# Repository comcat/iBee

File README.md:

iBee PCB Quadcopter
========================

[*iBee Quadcopter Board PCB Layout (iBee V0.8)*](https://www.jackslab.org/)

[*iBee Quadcopter Board PCB (iBee V0.8)*](https://www.jackslab.org/)

It's based on the control board of Flexbot Quadcopter.

Repository Contents
-------------------
* hardware/V0.8/ - All Eagle design files (.brd, .sch) and Gerber files of iBee version 0.8

License Information
-------------------
The hardware is released under [Creative Commons ShareAlike 4.0 International](https://creativecommons.org/licenses/by-sa/4.0/).

Distributed as-is; no warranty is given.

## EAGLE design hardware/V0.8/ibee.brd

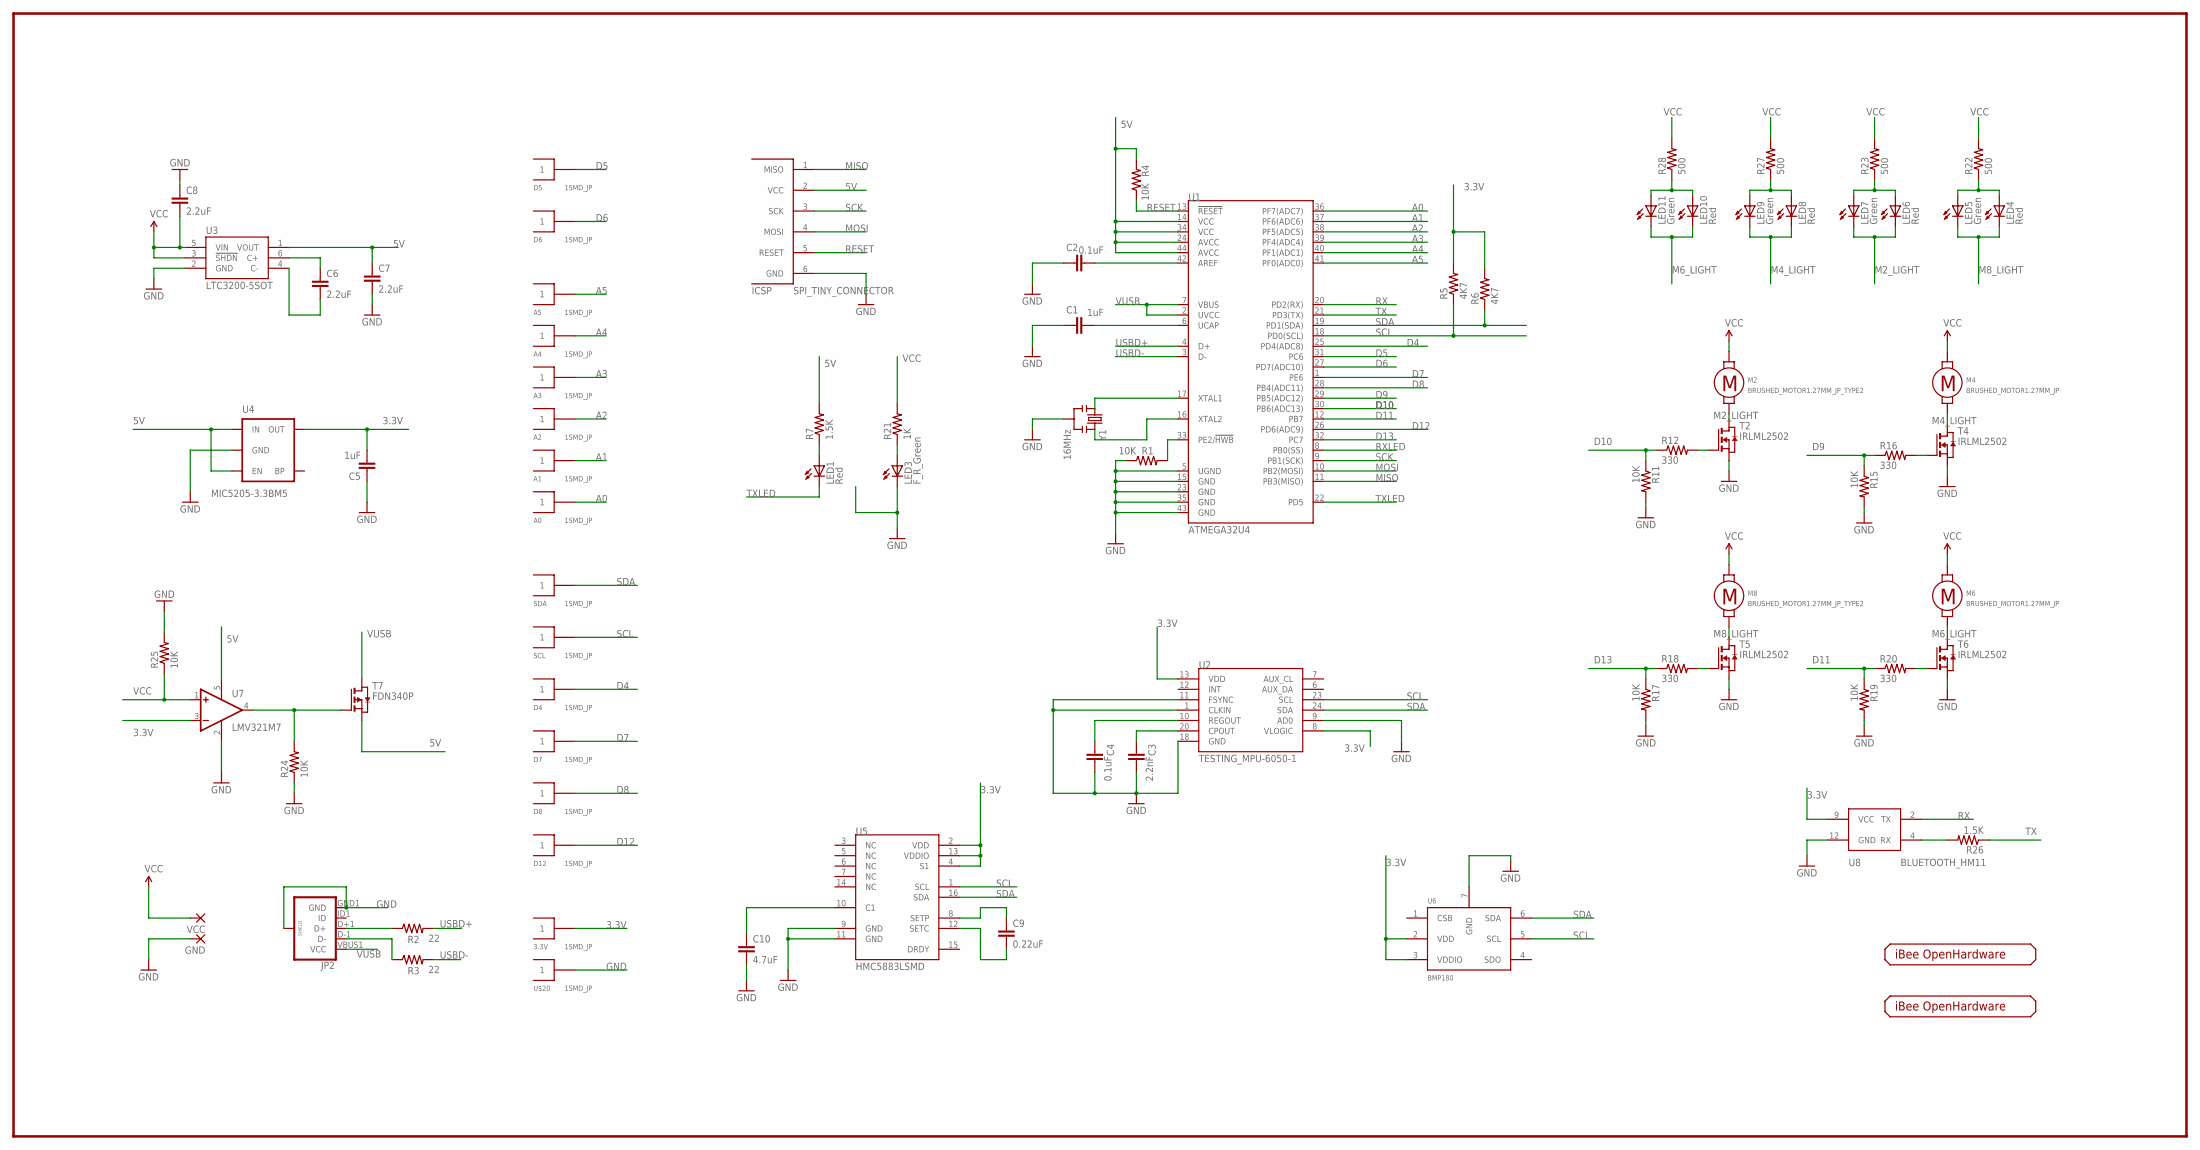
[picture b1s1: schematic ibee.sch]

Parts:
3.3V: 1SMD_JP; 1SMD
A0, A1, A2, A3, A4, A5: 1SMD_JP; 1SMD
C1, C5: 1uF; 0402-CAP
C2, C4: 0.1uF; 0402-CAP
C3: 2.2nF; 0402-CAP
C6, C7, C8: 2.2uF; 0603-CAP
C9: 0.22uF; 0402-CAP
C10: 4.7uF; 0603-CAP
D4, D5, D6, D7, D8, D12: 1SMD_JP; 1SMD
GND: 2,15/1,0
ICSP: SPI_TINY_CONNECTOR; AVR_ISP_TINY_CONNECTOR_NO_BORDER
JP2: USB_MICROB_PLUGCONN-11752; USB-B-MICRO-SMD_V03
LED1, LED4, LED6, LED8, LED10: Red; CHIPLED_0603
LED3: F_R_Green; CHIPLED_0603
LED5, LED7, LED9, LED11: Green; CHIPLED_0603
M2, M8: BRUSHED_MOTOR1.27MM_JP_TYPE2; BRUSHED_MOTOR_1.27MM_JP_TYPE2
M4, M6: BRUSHED_MOTOR1.27MM_JP; BRUSHED_MOTOR_1.27MM_JP
R1, R4, R11, R15, R17, R19, R24, R25: 10K; 0402-RES
R2, R3: 22; 0402-RES
R5, R6: 4K7; 0402-RES
R7, R26: 1.5K; 0402-RES
R12, R16, R18, R20: 330; 0402-RES
R21: 1K; 0402-RES
R22, R23, R27, R28: 500; 0402-RES
SCL: 1SMD_JP; 1SMD
SDA: 1SMD_JP; 1SMD
T2, T4, T5, T6: IRLML2502; SOT-23
T7: FDN340P; SOT23
U1: ATMEGA32U4; TESTING_QFN-44-7X7
U2: TESTING_MPU-6050-1; TESTING_QFN-24-4MM2
U3: LTC3200-5SOT; SOT23-6
U4: MIC5205-3.3BM5; SOT23-5
U5: HMC5883LSMD; TESTING_16LPCC
U6: BMP180
U7: LMV321M7; SC70-5L
U8: BLUETOOTH_HM11
U$1: IBEE-LOGO-T; IBEE-LOGO-TOP
U$2: IBEE-LOGO-B; FLEXBOT_LOGO_TYPE2
U$20: 1SMD_JP; 1SMD
VCC: 2,15/1,0
Y1: 16MHz; RESONATOR-SMD

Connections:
3.3V: 3.3V.1, C5.2, R5.2, R6.2, U2.8 (VLOGIC), U2.13 (VDD), U4.5 (OUT), U5.2 (VDD), U5.4 (S1), U5.13 (VDDIO), U6.2 (VDD), U6.3 (VDDIO), U7.3 (-IN), U8.9 (VCC)
5V: C7.1, ICSP.2 (VCC), R4.2, R7.2, T7.2 (S), U1.14 (VCC), U1.24 (AVCC), U1.34 (VCC), U1.44 (AVCC), U3.1 (VOUT), U4.1 (IN), U4.3 (EN), U7.5 (V+)
A0: A0.1, U1.36 (PF7(ADC7))
A1: A1.1, U1.37 (PF6(ADC6))
A2: A2.1, U1.38 (PF5(ADC5))
A3: A3.1, U1.39 (PF4(ADC4))
A4: A4.1, U1.40 (PF1(ADC1))
A5: A5.1, U1.41 (PF0(ADC0))
D4: D4.1, U1.25 (PD4(ADC8))
D5: D5.1, U1.31 (PC6)
D6: D6.1, U1.27 (PD7(ADC10))
D7: D7.1, U1.1 (PE6)
D8: D8.1, U1.28 (PB4(ADC11))
D9: R15.1, R16.1, U1.29 (PB5(ADC12))
D10: R11.1, R12.1, U1.30 (PB6(ADC13))
D11: R19.1, R20.1, U1.12 (PB7)
D12: D12.1, U1.26 (PD6(ADC9))
D13: R17.1, R18.1, U1.32 (PC7)
GND: C1.1, C2.1, C3.2, C4.2, C5.1, C7.2, C8.1, C10.2, GND.1, ICSP.6 (GND), JP2.GND1 (GND), JP2.SHIELD1 (SHIELD), JP2.SHIELD2 (SHIELD), JP2.SHIELD3 (SHIELD), LED3.C, R1.1, R11.2, R15.2, R17.2, R19.2, R24.1, R25.2, T2.2 (S), T4.2 (S), T5.2 (S), T6.2 (S), U1.5 (UGND), U1.15 (GND), U1.23 (GND), U1.35 (GND), U1.43 (GND), U2.1 (CLKIN), U2.9 (AD0), U2.11 (FSYNC), U2.18 (GND), U3.2 (GND), U4.2 (GND), U5.9 (GND), U5.11 (GND), U6.7 (GND), U7.2 (V-), U8.12 (GND), U$20.1, Y1.2
M2_LIGHT: LED6.C, LED7.C, M2.P$1 (1), T2.1 (D)
M4_LIGHT: LED8.C, LED9.C, M4.P$1 (1), T4.1 (D)
M6_LIGHT: LED10.C, LED11.C, M6.P$1 (1), T6.1 (D)
M8_LIGHT: LED4.C, LED5.C, M8.P$1 (1), T5.1 (D)
MISO: ICSP.1 (MISO), U1.11 (PB3(MISO))
MOSI: ICSP.4 (MOSI), U1.10 (PB2(MOSI))
unnamed: U1.17 (XTAL1), Y1.1
unnamed: U1.16 (XTAL2), Y1.3
unnamed: JP2.D+1 (D+), R2.1
unnamed: JP2.D-1 (D-), R3.1
unnamed: C1.2, U1.6 (UCAP)
unnamed: C2.2, U1.42 (AREF)
unnamed: C4.1, U2.10 (REGOUT)
unnamed: C3.1, U2.20 (CPOUT)
unnamed: LED1.A, R7.1
unnamed: R1.2, U1.33 (PE2/!HWB)
unnamed: R18.2, T5.3 (G)
unnamed: LED3.A, R21.1
unnamed: R12.2, T2.3 (G)
unnamed: LED8.A, LED9.A, R27.1
unnamed: R16.2, T4.3 (G)
unnamed: LED10.A, LED11.A, R28.1
unnamed: LED6.A, LED7.A, R23.1
unnamed: C9.1, U5.8 (SETP)
unnamed: LED4.A, LED5.A, R22.1
unnamed: C6.1, U3.6 (C+)
unnamed: C6.2, U3.4 (C-)
unnamed: C9.2, U5.12 (SETC)
unnamed: C10.1, U5.10 (C1)
unnamed: R20.2, T6.3 (G)
unnamed: R24.2, T7.3 (G), U7.4 (OUT)
unnamed: R26.2, U8.4 (RX)
RESET: ICSP.5 (RESET), R4.1, U1.13 (!RESET)
RX: U1.20 (PD2(RX)), U8.2 (TX)
RXLED: U1.8 (PB0(SS))
SCK: ICSP.3 (SCK), U1.9 (PB1(SCK))
SCL: R5.1, SCL.1, U1.18 (PD0(SCL)), U2.23 (SCL), U5.1 (SCL), U6.5 (SCL)
SDA: R6.1, SDA.1, U1.19 (PD1(SDA)), U2.24 (SDA), U5.16 (SDA), U6.6 (SDA)
TX: R26.1, U1.21 (PD3(TX))
TXLED: LED1.C, U1.22 (PD5)
USBD+: R2.2, U1.4 (D+)
USBD-: R3.2, U1.3 (D-)
VCC: C8.2, M2.P$2 (2), M4.P$2 (2), M6.P$2 (2), M8.P$2 (2), R21.2, R22.2, R23.2, R25.1, R27.2, R28.2, U3.3 (!SHDN), U3.5 (VIN), U7.1 (+IN), VCC.1
VUSB: JP2.VBUS1 (VCC), T7.1 (D), U1.2 (UVCC), U1.7 (VBUS)

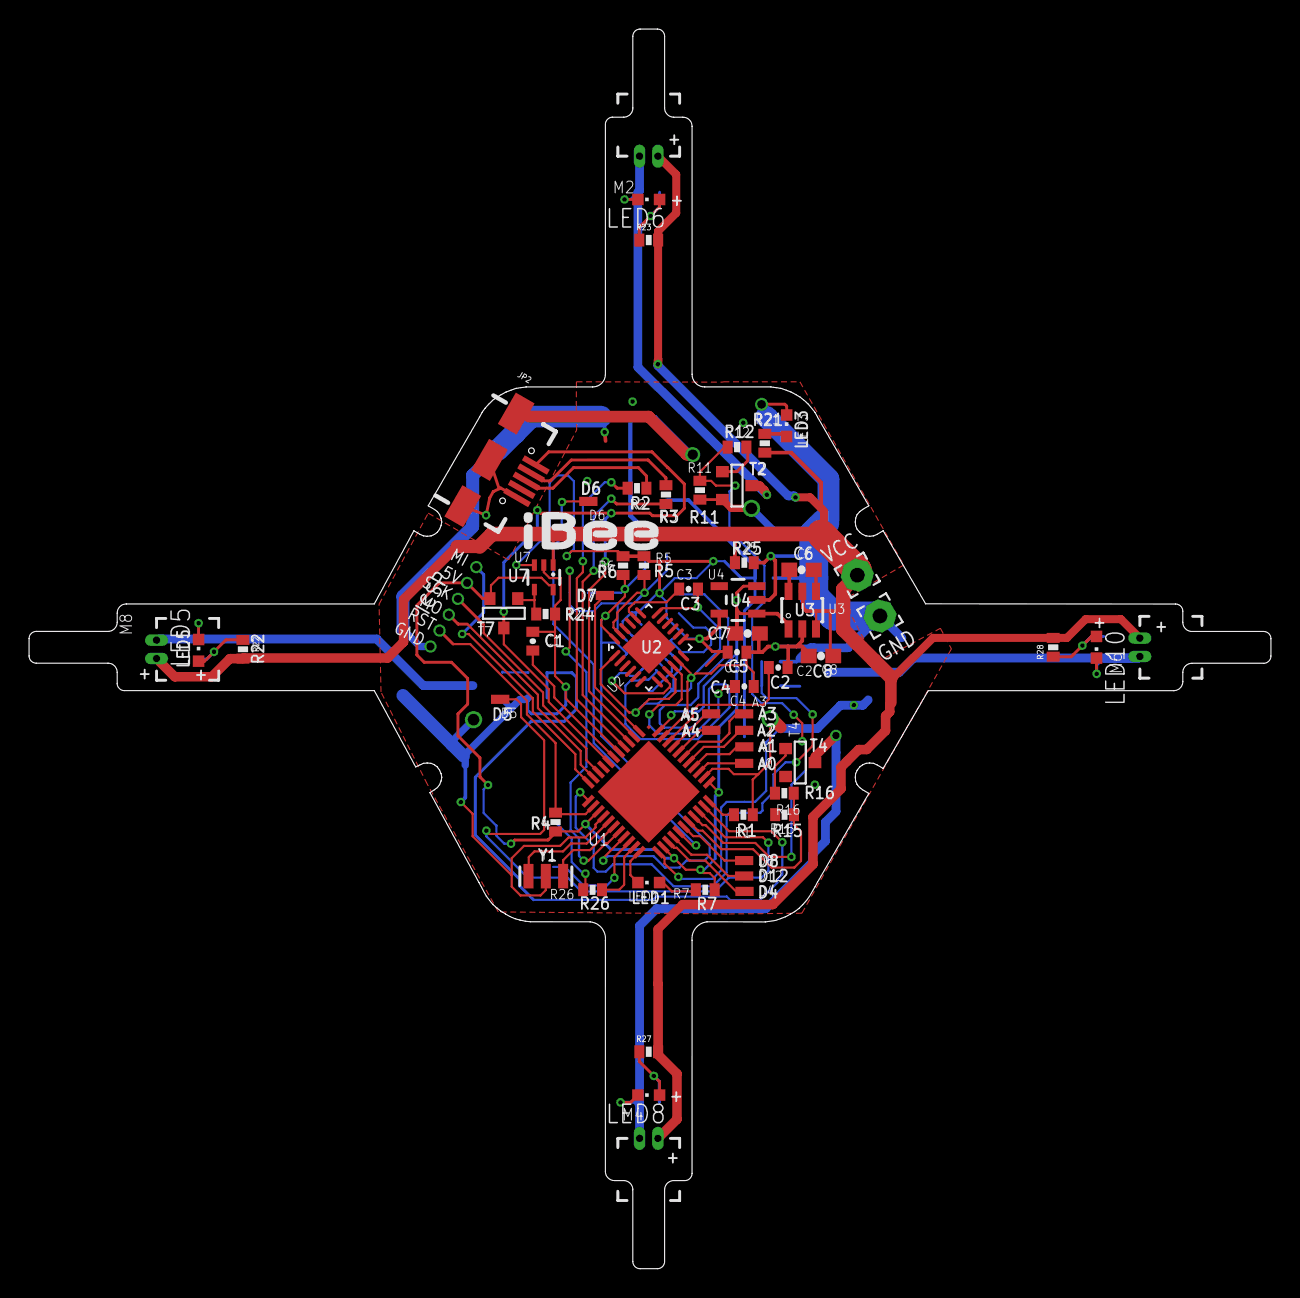
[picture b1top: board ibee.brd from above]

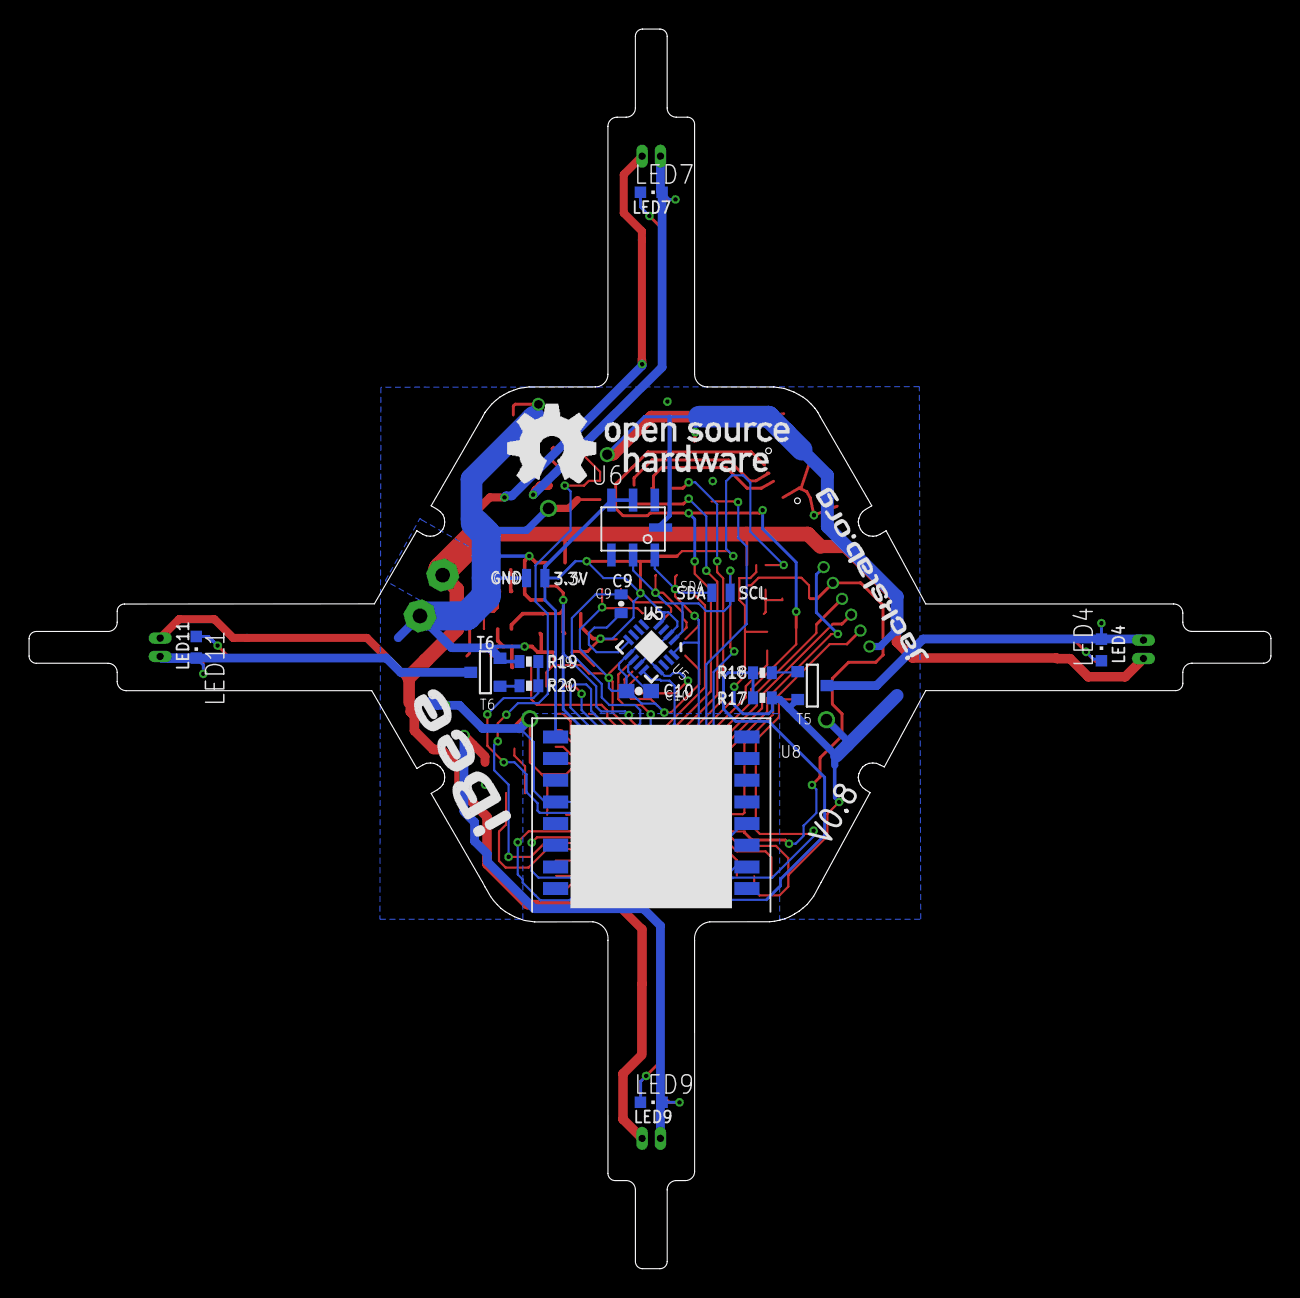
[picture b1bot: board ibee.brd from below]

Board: 2 copper layers, 86.0 x 85.8 mm, 83 parts (20 on the bottom side), 62 nets.

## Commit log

2016-07-27 add the design files of version 0.8
2016-07-27 add the readme
2016-07-27 update readme and add a pcb image
2017-01-25 add the bootloader of the atmega32u4
    'make flash' to flash the bootloader
2017-01-25 add the HexNanoMWC_Quad firmware
    Upstream is flexbot v1.1.2

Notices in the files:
parts and their libraries:
SparkFun-FreqCtrl: Licensing: CC v3.0 Share-Alike You are welcome to use this library for commercial purposes.
